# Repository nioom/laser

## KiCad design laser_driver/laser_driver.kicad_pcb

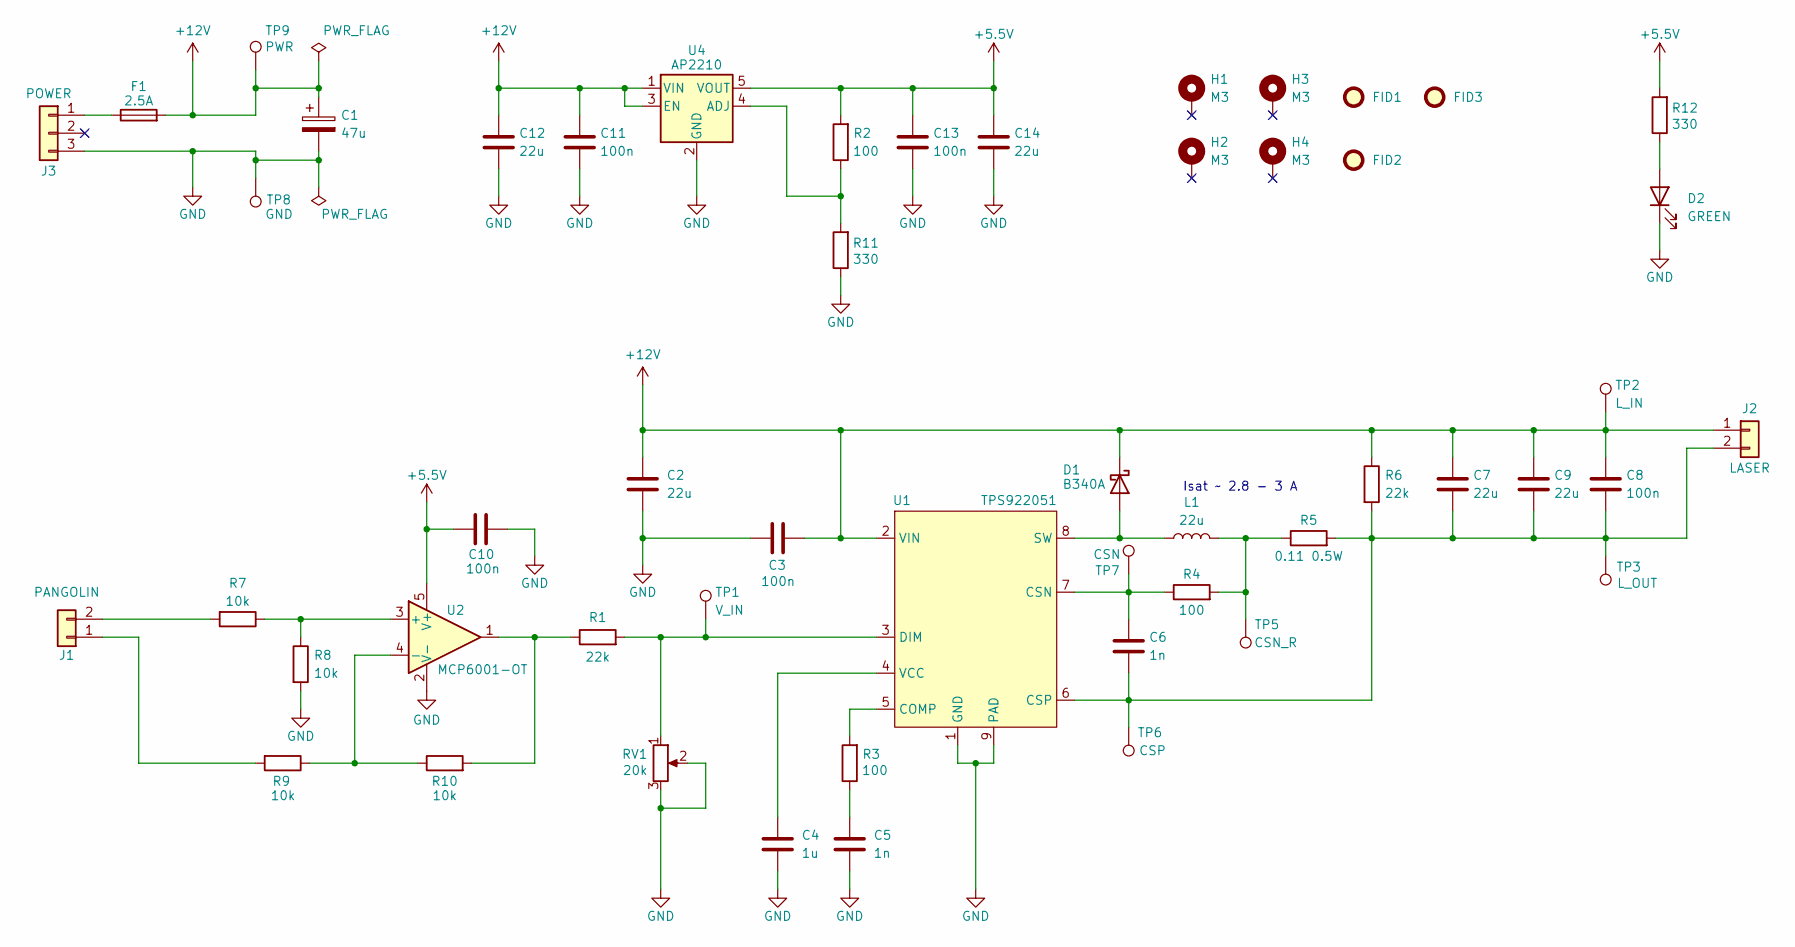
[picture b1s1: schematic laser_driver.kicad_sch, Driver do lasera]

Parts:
C1: 47u; CP_Elec_6.3x5.3
C2, C7, C9, C12, C14: 22u; C_1210_3225Metric_Pad1.33x2.70mm_HandSolder
C3, C8, C10, C11, C13: 100n; C_0603_1608Metric_Pad1.08x0.95mm_HandSolder
C4: 1u; C_0603_1608Metric_Pad1.08x0.95mm_HandSolder
C5, C6: 1n; C_0603_1608Metric_Pad1.08x0.95mm_HandSolder
D1: B340A; D_SMA
D2: GREEN; D_0603_1608Metric_Pad1.05x0.95mm_HandSolder
F1: 2.5A; Fuse_1206_3216Metric_Pad1.42x1.75mm_HandSolder
FID1, FID2, FID3: Fiducial_1mm_Mask2mm
H1, H2, H3, H4: M3; MountingHole_3.2mm_M3_ISO7380_Pad
J1: PANGOLIN; JST_PH_B2B-PH-K_1x02_P2.00mm_Vertical
J2: LASER; Molex_KK-396_5273-02A_1x02_P3.96mm_Vertical
J3: POWER; Molex_KK-396_5273-03A_1x03_P3.96mm_Vertical
L1: 22u; MGAH0603220M-10
R1, R6: 22k; R_0603_1608Metric_Pad0.98x0.95mm_HandSolder
R2, R3, R4: 100; R_0603_1608Metric_Pad0.98x0.95mm_HandSolder
R5: 0.11 0.5W; R_1206_3216Metric
R7, R8, R9, R10: 10k; R_0603_1608Metric_Pad0.98x0.95mm_HandSolder
R11, R12: 330; R_0603_1608Metric_Pad0.98x0.95mm_HandSolder
RV1: 20k; Potentiometer_Bourns_3296W_Vertical
TP1: V_IN; TestPoint_Pad_D1.5mm
TP2: L_IN; TestPoint_Pad_D1.5mm
TP3: L_OUT; TestPoint_Pad_D1.5mm
TP5: CSN_R; TestPoint_Pad_D1.5mm
TP6: CSP; TestPoint_Pad_D1.5mm
TP7: CSN; TestPoint_Pad_D1.5mm
TP8: GND; TestPoint_Pad_D1.5mm
TP9: PWR; TestPoint_Pad_D1.5mm
U1: TPS922051; HVSSOP-8-1EP_3x3mm_P0.65mm_EP1.57x1.89mm_ThermalVias
U2: MCP6001-OT; SOT-23-5
U4: AP2210; SOT-23-5

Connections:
+5.5V: C10.1, C13.1, C14.1, R2.2, R12.2, U2.5 (V+), U4.5 (VOUT)
+12V: C1.1, C2.1, C3.2, C7.1, C8.1, C9.1, C11.1, C12.1, D1.1 (K), F1.2, J2.1, R6.1, TP2.1, TP9.1, U1.2 (VIN), U4.1 (VIN), U4.3 (EN)
GND: C1.2, C2.2, C3.1, C4.2, C5.2, C10.2, C11.2, C12.2, C13.2, C14.2, D2.1 (K), J3.3, R8.2, R11.1, RV1.2, RV1.3, TP8.1, U1.1 (GND), U1.9 (PAD), U2.2 (V-), U4.2 (GND)
unnamed: C5.1, R3.1
unnamed: D1.2 (A), L1.1, U1.8 (SW)
unnamed: D2.2 (A), R12.1
unnamed: J1.1, R9.2
unnamed: J1.2, R7.2
unnamed: C6.2, C7.2, C8.2, C9.2, J2.2, R5.2, R6.2, TP3.1, TP6.1, U1.6 (CSP)
unnamed: F1.1, J3.1
unnamed: L1.2, R4.2, R5.1, TP5.1
unnamed: R1.1, R10.2, U2.1
unnamed: R3.2, U1.5 (COMP)
unnamed: C6.1, R4.1, TP7.1, U1.7 (CSN)
unnamed: R1.2, RV1.1, TP1.1, U1.3 (DIM)
unnamed: C4.1, U1.4 (VCC)
unnamed: R7.1, R8.1, U2.3 (+)
unnamed: R9.1, R10.1, U2.4 (-)
unnamed: R2.1, R11.2, U4.4 (ADJ)

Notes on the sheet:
Isat ~ 2.8 - 3 A

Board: 2 copper layers, 52 parts (0 on the bottom side), 19 nets, no tracks yet.

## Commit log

2025-12-18 Ignoruje backupy
2025-12-18 KiCad
2025-12-18 Dokumentacja
2025-12-21 Poprawiony schemat oraz wartości komponentów
2025-12-25 Poprawki do schematu oraz dobór footprintów i BOM
2025-12-26 Ostatnie poprawki do schematu
2025-12-27 Teraz już na pewno statnie poprawki do schematu
